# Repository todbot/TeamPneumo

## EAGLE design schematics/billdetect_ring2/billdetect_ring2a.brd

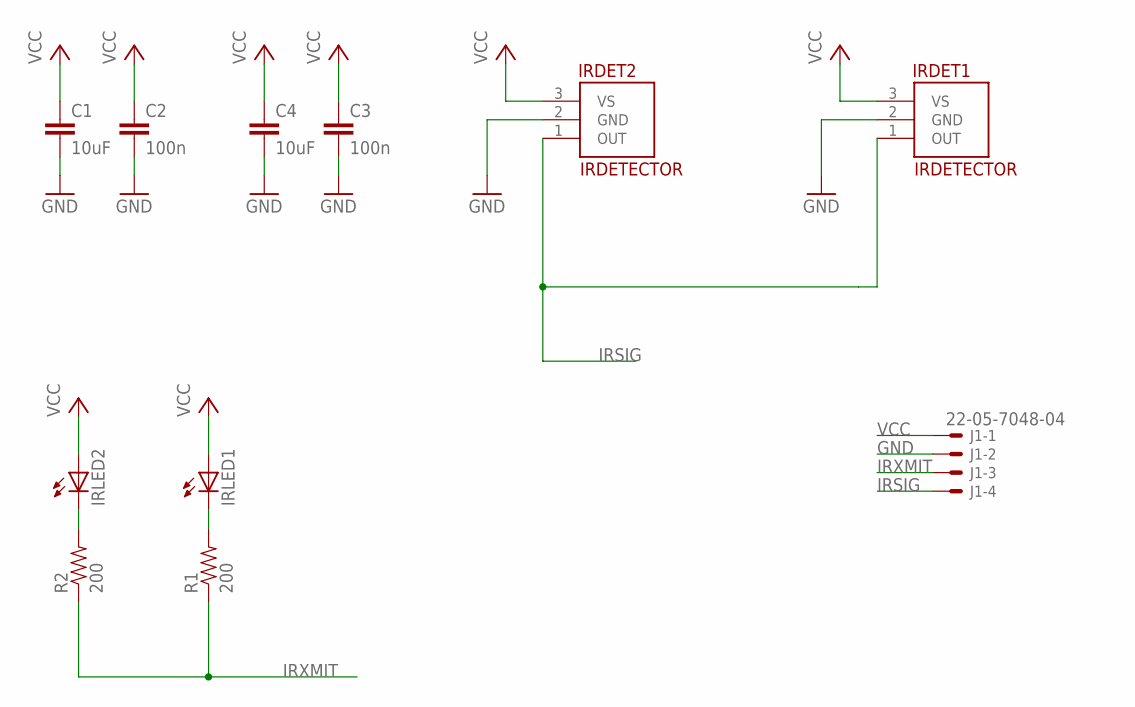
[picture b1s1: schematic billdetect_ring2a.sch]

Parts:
C1, C4: 10uF; 0805
C2, C3: 100n; 0805
IRDET1, IRDET2: IRDETECTOR; TSOP-3PIN-2.54MM
IRLED1, IRLED2: LED-5MM-90DEG
J1: 22-05-7048-04; 7395-04
R1, R2: 200; 0805

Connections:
GND: C1.2, C2.2, C3.2, C4.2, IRDET1.2 (GND), IRDET2.2 (GND), J1.2
IRSIG: IRDET1.1 (OUT), IRDET2.1 (OUT), J1.4
IRXMIT: J1.3, R1.1, R2.1
unnamed: IRLED2.K (C), R2.2
unnamed: IRLED1.K (C), R1.2
VCC: C1.1, C2.1, C3.1, C4.1, IRDET1.3 (VS), IRDET2.3 (VS), IRLED1.A, IRLED2.A, J1.1

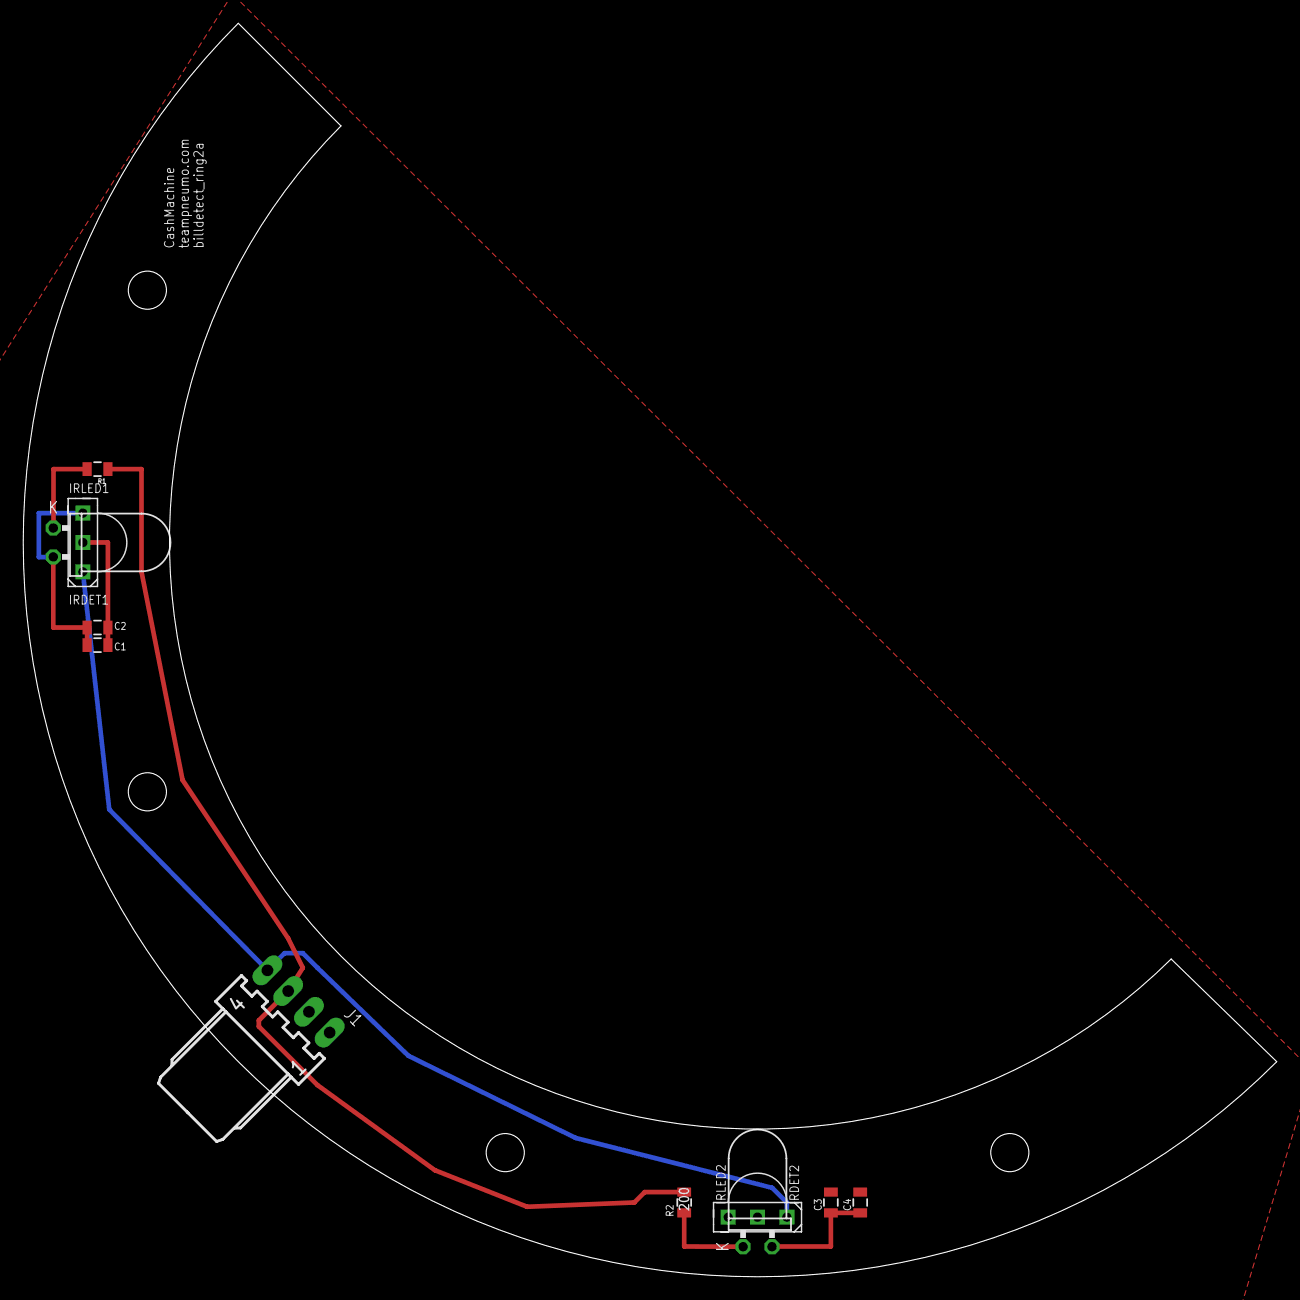
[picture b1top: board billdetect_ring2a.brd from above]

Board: 2 copper layers, 108.5 x 108.5 mm, 15 parts (0 on the bottom side), 6 nets.

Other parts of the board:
U$1, U$3, U$5, U$6: STAND-OFF

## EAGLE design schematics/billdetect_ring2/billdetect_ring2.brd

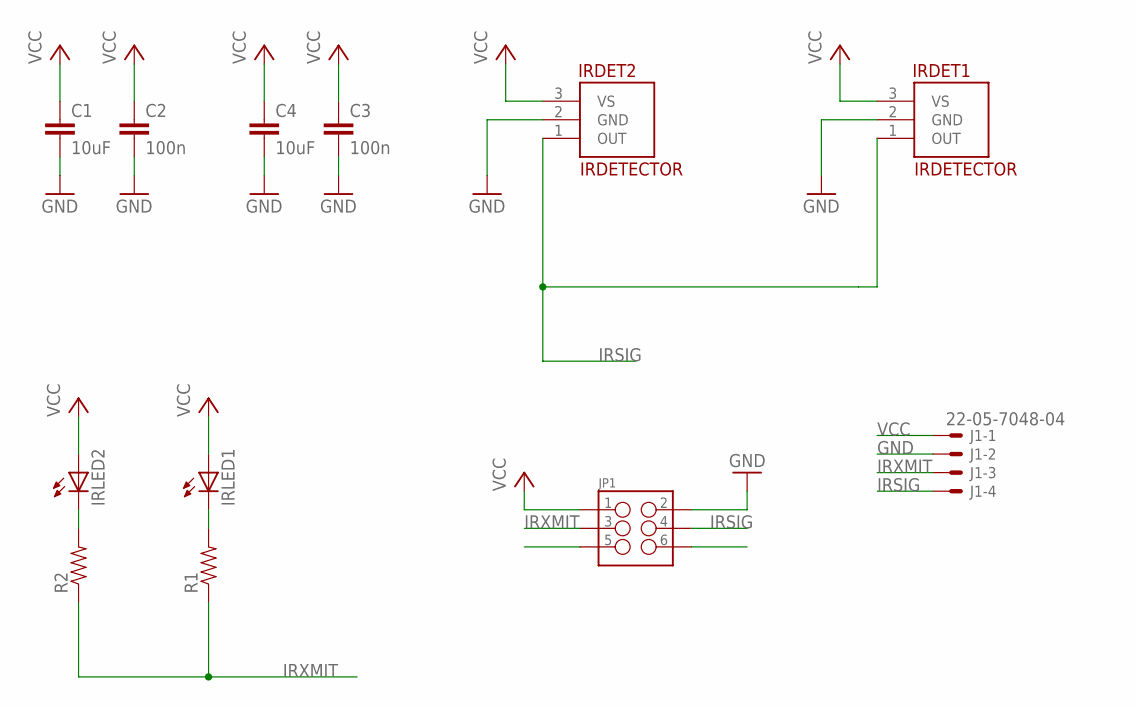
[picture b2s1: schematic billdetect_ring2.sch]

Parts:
C1, C4: 10uF; 0805
C2, C3: 100n; 0805
IRDET1, IRDET2: IRDETECTOR; TSOP-3PIN-2.54MM
IRLED1, IRLED2: LED-5MM-90DEG
J1: 22-05-7048-04; 7395-04
JP1: M03X22X3_SILK_SM; 2X3
R1, R2: RESISTOR0805-RES; 0805

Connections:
GND: C1.2, C2.2, C3.2, C4.2, IRDET1.2 (GND), IRDET2.2 (GND), J1.2, JP1.2
IRSIG: IRDET1.1 (OUT), IRDET2.1 (OUT), J1.4, JP1.4
IRXMIT: J1.3, JP1.3, R1.1, R2.1
unnamed: IRLED2.K (C), R2.2
unnamed: IRLED1.K (C), R1.2
VCC: C1.1, C2.1, C3.1, C4.1, IRDET1.3 (VS), IRDET2.3 (VS), IRLED1.A, IRLED2.A, J1.1, JP1.1

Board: 2 copper layers, 16 parts (1 on the bottom side), 6 nets, no tracks yet.

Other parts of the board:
U$1, U$3, U$5, U$6: STAND-OFF

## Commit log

2011-08-19 added billdetector1 schematics, added BillDetectorTest6 firmware, added some docs
2011-08-19 small doc change
2011-08-19 new version of billdetector, this one with servo outputs and mosfet drive and i2c.
2011-08-21 added billdetectortest7, uses eventfuse scheduler library
2011-08-22 moved EventFuse library local
2011-08-24 Remote Control Files - Noncommented
    The code currently running on the remote control and the schematics for
    the two different ideas for controlling it (we went with relays)
2011-08-28 new billdetectorv1 based on billdetectortest7, version demoed to mark
2011-08-28 and added SoftwareServo.cpp
2011-08-28 and added SoftwareServo.h
2011-09-30 bell ringer working as expected, revamped "doingThings" (need a better name) event system
2011-09-30 how did .svn files get in here
2011-09-30 added softwareservo.disable() to temporarily disable updating of a servo, to keep bellringer from jittering
2011-10-06 added HandDetectorV1
2011-10-16 version of handdetectorv1 that is on for NCM block party
2011-10-17 Pictures for wiring up remote control
    Two pictures for use in wiring up remote control.
2011-10-17 added annotated version of backOfRemote.jpg
2011-10-18 added simple test of modded long ranger iii remote with custom relay shield
2011-10-18 moved to hardware Servo library in Arduino core (it only uses Timer1, not Timer2), removed TimePin.h as not used anymore
2011-10-18 added camera flash detector
2011-10-18 removed SoftwareServo references, misc cleanup, added BeamBreaker_{enable,disable}AllIR() funcs
2011-10-18 fixed indentation
2011-10-21 added ServoEasingTests attempting to using Easing library in non-blocking way
2011-10-21 added new easeTo() support to ServoEaser
2011-10-21 made library bundle for ServoEaser
2011-10-21 dammit more svn dirs
2011-10-21 cleaned up BeamBreaker a bit
2011-10-21 added new arrivedfunc callback, added servoEaserTest3 to show off callback functionality
2011-10-21 moved to repo todbot/ServoEaser
2011-10-21 added note about moved ServoEaser
2011-10-27 HandDetectorV1 as installed at NCM 26 Oct 2011
2012-02-08 HandTriggerTxV1 shipped to NCM, works with xbee
2012-05-09 new billdetector for big objects
2012-05-11 billdetectorv2 installed on two big pieces
2012-05-11 synced up old billdetectorv1 with new beambreaker.h
2013-08-06 long overdue syncup with local repo
2015-01-25 added some new things, document some old

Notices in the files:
parts and their libraries:
SparkFun-Passives: Licensing: CC v3.0 Share-Alike You are welcome to use this library for commercial purposes.
